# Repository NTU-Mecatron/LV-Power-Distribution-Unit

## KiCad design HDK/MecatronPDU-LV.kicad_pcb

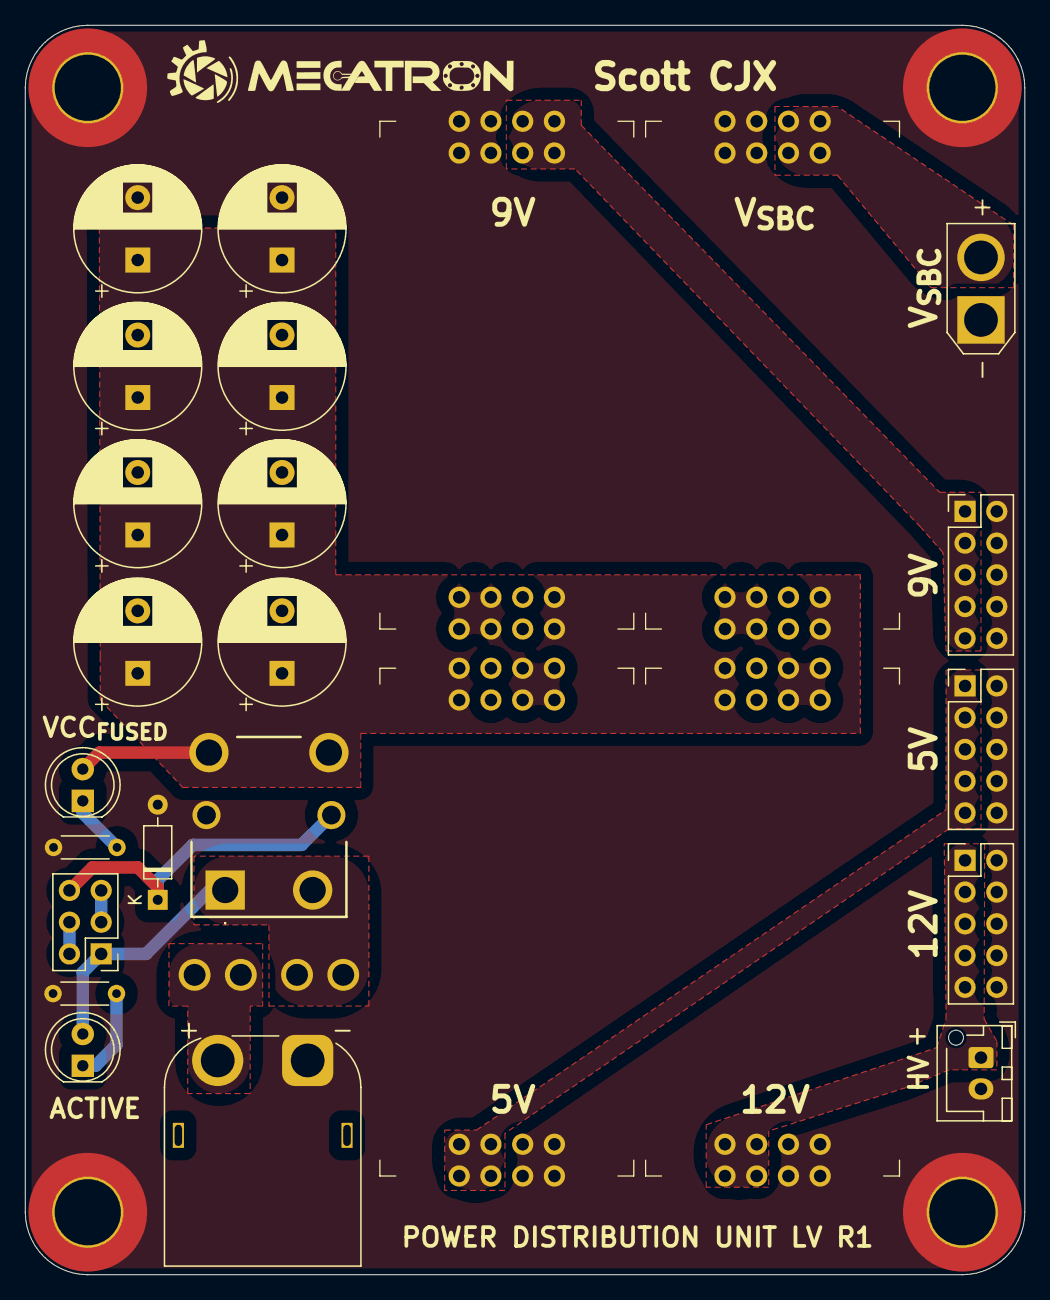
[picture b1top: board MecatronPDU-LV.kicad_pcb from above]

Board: 2 copper layers, 80.0 x 100.0 mm, 30 parts (0 on the bottom side), 13 nets.

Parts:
C101, C102, C103, C104, C105, C106, C107, C108: 560u; CP_Radial_D10.0mm_P5.00mm
D101: D; D_DO-35_SOD27_P7.62mm_Horizontal
D102, D103: LED; LED_D5.0mm
F101: Fuse; FUSE-MCCQ-122
H101, H102, H103, H104: MountingHole_Pad_MP; MountingHole_5.3mm_M5_ISO7380_Pad_TopBottom
J101: Power In; AMASS_XT60PW-M_1x02_P7.20mm_Horizontal
J102: E-Stops; PinHeader_2x03_P2.54mm_Vertical
J201: V_{HV}; JST_XH_B2B-XH-AM_1x02_P2.50mm_Vertical
J202, J203, J204: V; PinHeader_2x05_P2.54mm_Vertical
J205: V_{SBC}; AMASS_XT30U-M_1x02_P5.0mm_Vertical
K101: Relay_SPST-NO; G8PM1AW7RDC12
R101, R102: 2k; R_Axial_DIN0204_L3.6mm_D1.6mm_P5.08mm_Horizontal
U201, U202, U203, U204: TPS5460 康威科技

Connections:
+5V: J202.1, J202.3, J202.5, J202.7, J202.9, U202.2 (V_{OUT})
+9V: J203.1, J203.3, J203.5, J203.7, J203.9, U203.2 (V_{OUT})
+12V: J201.1, J204.1, J204.3, J204.5, J204.7, J204.9, U204.2 (V_{OUT})
/VCC_FUSE: D103.2 (A), F101.2, J102.1, K101.14
GND: C101.2, C102.2, C103.2, C104.2, C105.2, C106.2, C107.2, C108.2, D101.2 (A), H101.1, H102.1, H103.1, H104.1, J101.1, J201.2, J202.2, J202.4, J202.6, J202.8, J202.10, J203.2, J203.4, J203.6, J203.8, J203.10, J204.2, J204.4, J204.6, J204.8, J204.10, J205.1, K101.A2, R101.2, R102.2, U201.G (GND), U202.G (GND), U203.G (GND), U204.G (GND)
unnamed: D101.1 (K), J102.6, K101.A1
unnamed: D102.1 (K), R101.1
unnamed: D103.1 (K), R102.1
unnamed: J102.2, J102.4
unnamed: J102.3, J102.5
VCC: F101.1, J101.2
VCCF: C101.1, C102.1, C103.1, C104.1, C105.1, C106.1, C107.1, C108.1, D102.2 (A), K101.13, U201.1 (V_{IN}), U202.1 (V_{IN}), U203.1 (V_{IN}), U204.1 (V_{IN})
V_{SBC}: J205.2, U201.2 (V_{OUT})

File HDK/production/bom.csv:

Designator,Footprint,Quantity,Value,LCSC Part #
"C101, C102, C103, C104, C105, C106, C107, C108",CP_Radial_D10.0mm_P5.00mm,8,560u,
D101,D_DO-35_SOD27_P7.62mm_Horizontal,1,D,
"D102, D103",LED_D5.0mm,2,LED,
F101,FUSE-MCCQ-122,1,Fuse,
J101,AMASS_XT60PW-M_1x02_P7.20mm_Horizontal,1,Power In,
J102,PinHeader_2x03_P2.54mm_Vertical,1,E-Stops,
J201,JST_XH_B2B-XH-AM_1x02_P2.50mm_Vertical,1,V_{HV},
"J202, J203, J204",PinHeader_2x05_P2.54mm_Vertical,3,V,
J205,AMASS_XT30U-M_1x02_P5.0mm_Vertical,1,V_{SBC},
K101,G8PM1AW7RDC12,1,Relay_SPST-NO,
"R101, R102",R_Axial_DIN0204_L3.6mm_D1.6mm_P5.08mm_Horizontal,2,2k,
"U201, U202, U203, U204",TPS5460 康威科技,4,TPS5460 康威科技,

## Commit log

2024-09-18 added r1
2024-09-18 updated docs
2024-09-18 updated prod
2024-09-18 updated sch docs
2024-09-18 Deployed ffe23d7 with MkDocs version: 1.6.1

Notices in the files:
HDK/MecatronPDU-LV.kicad_pcb:
License :CERN-OHL-S-2.0
Copyright © Mecatron
